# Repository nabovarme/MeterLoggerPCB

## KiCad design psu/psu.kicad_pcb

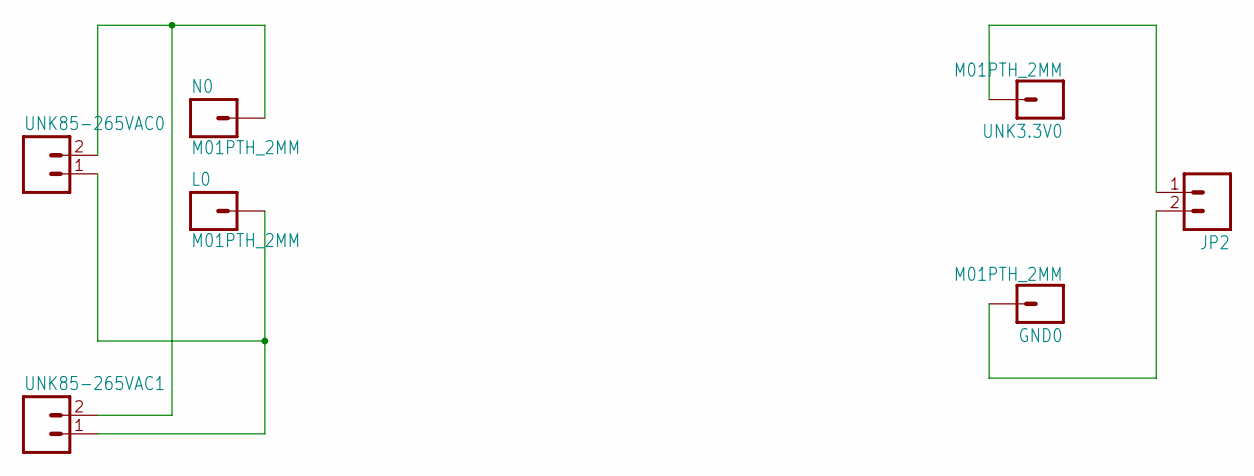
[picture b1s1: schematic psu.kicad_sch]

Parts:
GND0: M01PTH_2MM; 1X01_2MM
JP2: M02PTH3_5MM; 1X02_LONGPADS
L0: M01PTH_2MM; 1X01_2MM
N0: M01PTH_2MM; 1X01_2MM
UNK3.3V0: M01PTH_2MM; 1X01_2MM
UNK85-265VAC0, UNK85-265VAC1: M02PTH3_5MM; 1X02_LONGPADS

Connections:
unnamed: L0.1, UNK85-265VAC0.1, UNK85-265VAC1.1
unnamed: N0.1, UNK85-265VAC0.2, UNK85-265VAC1.2
unnamed: JP2.1, UNK3.3V0.1
unnamed: GND0.1, JP2.2

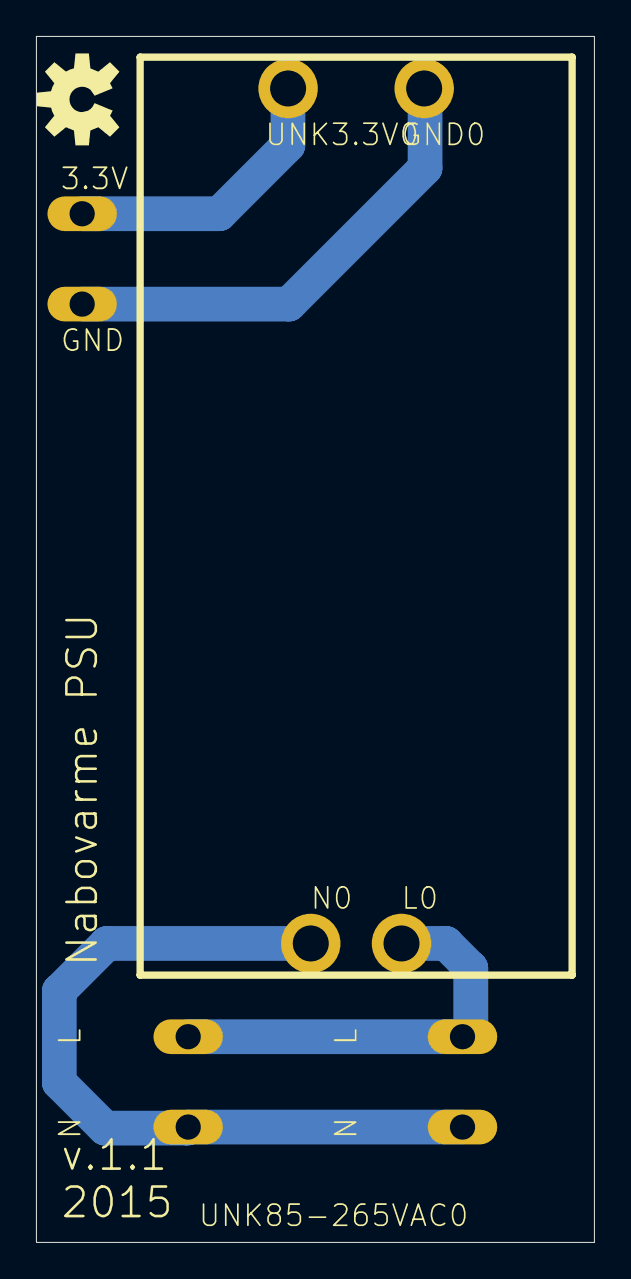
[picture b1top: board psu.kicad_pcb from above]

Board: 2 copper layers, 31.0 x 67.0 mm, 8 parts (0 on the bottom side), 4 nets.

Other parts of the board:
U$1: OSHW-LOGO-M

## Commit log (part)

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2015-09-15 added pcb+power from f81b98b96438f6aeb28dbc087c39275dec301eaf
2016-05-18 v.1.2.1
    + watchdog and pulldown on gpio 15
2016-05-29 PCB: v.1.4.1 Added FeRAM
    + docs
2016-11-19 added pull up resistor on GPIO02
2017-04-21 added missing pull down (R12) on pcb
2017-04-23 reverted pcb to v 1.2.1 2377baf1af9bc101ab4e1265beb616f56084d54c no pull down needed
2017-10-08 Labels for N and L on AC in/out
2017-10-09 pcb board made 8 mm higher for better fixation in kamstrup meter
2017-10-17 updated pdf's
    for schematics and pcb
2017-10-17 moved meterlogger_doxygen to submodule
2017-10-17 moved pcb/psu to pcb+power/psu
2017-10-19 RS # for R4, R5, R8, R9 changed
2017-10-23 Missing R11 value fixed
2017-10-23 version bumbed to 1.2.5
2017-10-25 rotated jp1, jp3 and jp3
2017-10-25 removed snubber circuits and external watchdog timer ic now version 1.3.0
2017-10-25 changed some via size v 1.3.1
2017-10-25 updated pdfs from latest version (v.1.3.1)
2018-04-27 updated psi pcb
    3.3V -> 3.6V
    v.1.1 -> v.1.2
    2015 -> 2018
2018-04-28 psu pcb: smaller holes for psu module
2018-04-28 psi pcb: better silk layout
2018-05-09 programmer connector moved
2018-05-11 Sdcard
2018-05-11 Silk updated
2018-05-11 Version sent to pcb fabrication
